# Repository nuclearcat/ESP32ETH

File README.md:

# ESP32ETH
Simple ESP32 with native ethernet using LAN8720 phy, Arduino compatible

Minimalistic design that can be extended. Manufactured and tested in real life, reliable, no packetloss, etc.

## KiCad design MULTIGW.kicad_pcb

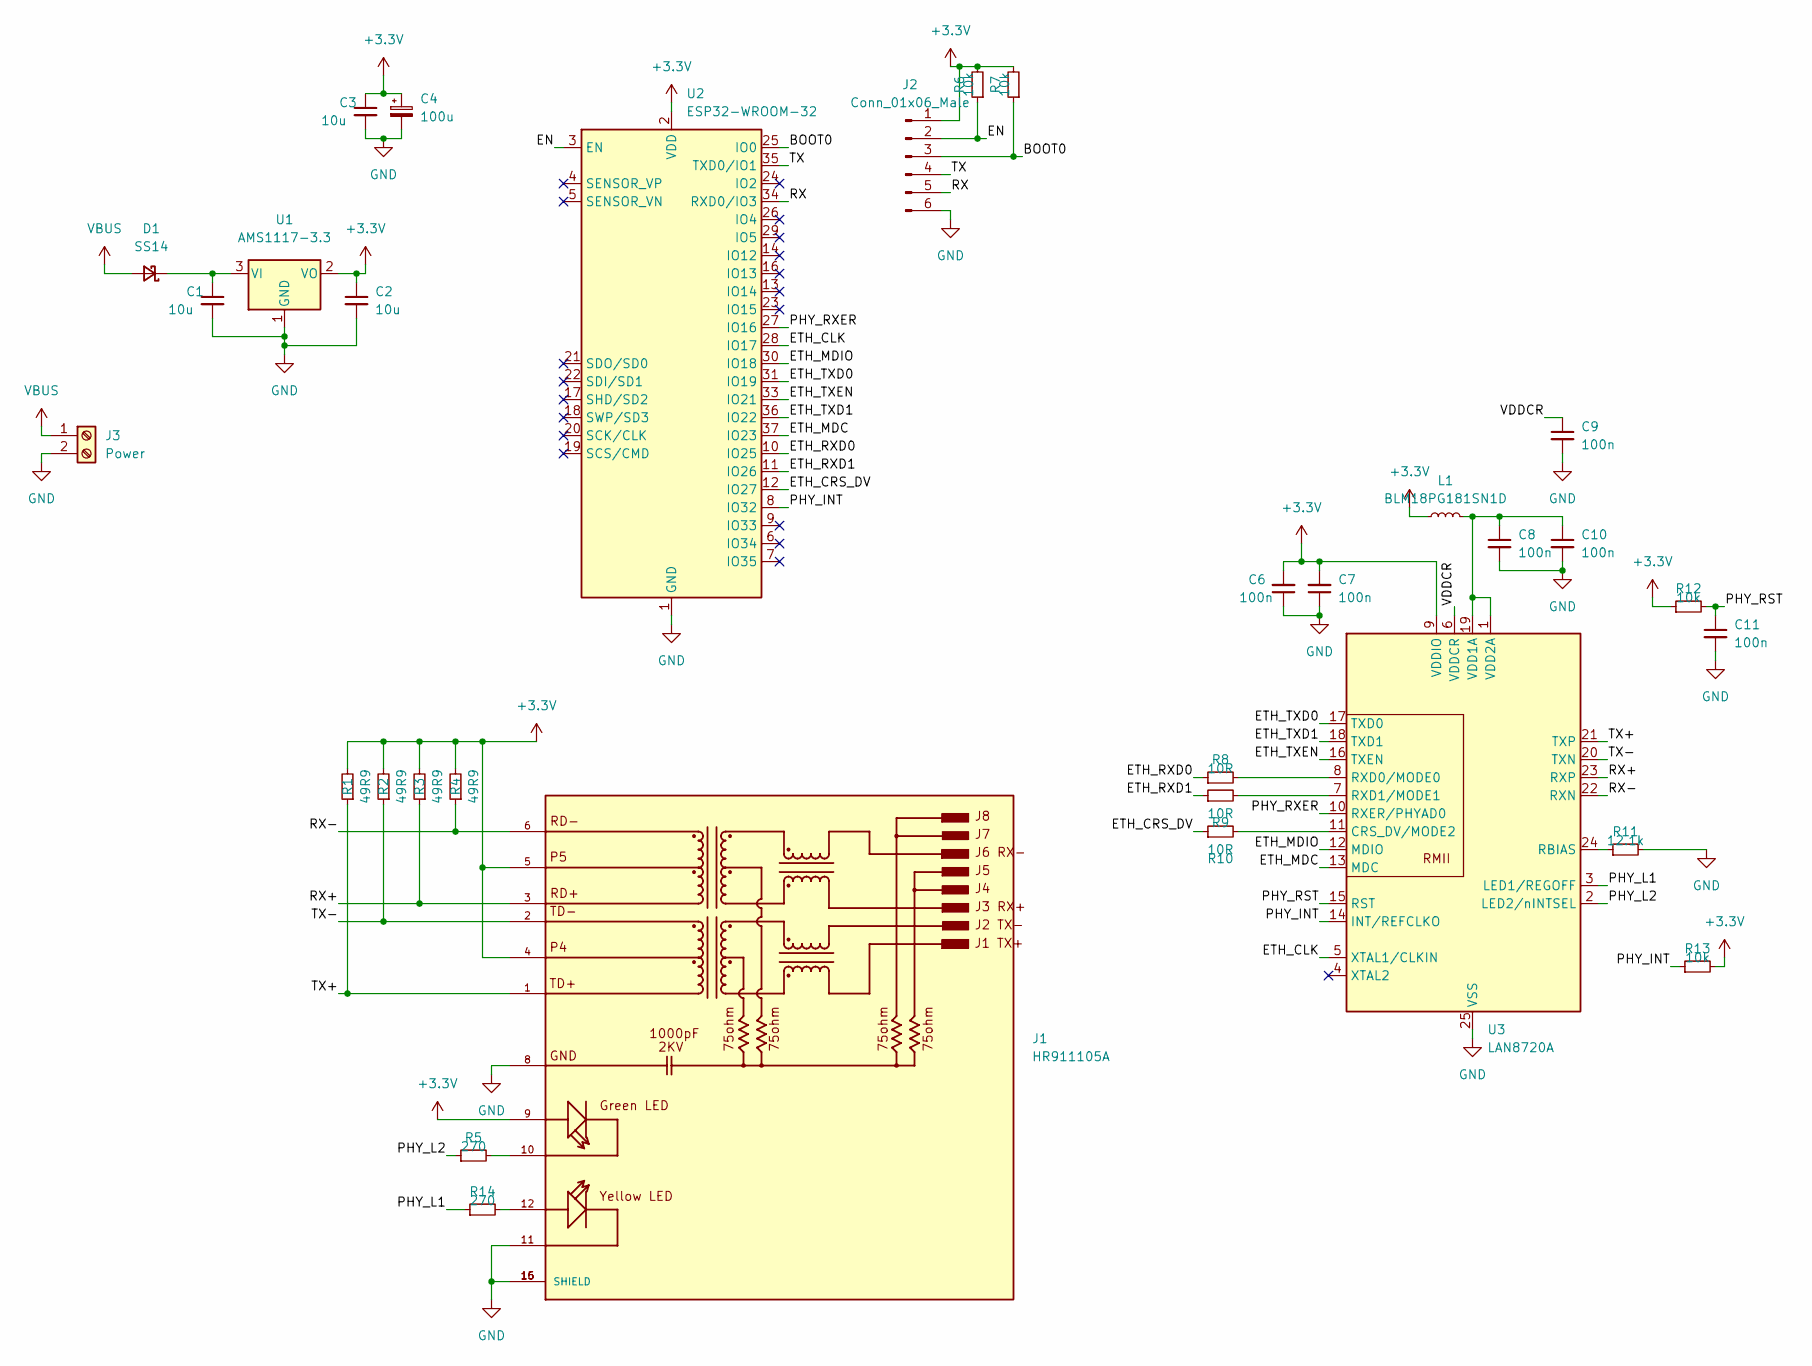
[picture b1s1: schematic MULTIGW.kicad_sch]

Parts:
C1: 10u; R_0603_1608Metric
C2, C3: 10u; C_0603_1608Metric
C4: 100u; CP_EIA-3528-21_Kemet-B
C6, C7, C8, C9, C10, C11: 100n; C_0603_1608Metric
D1: SS14; D_SMA
J1: HR911105A; HANRUN_HR911105A; PARTREV A
J2: Conn_01x06_Male; PinHeader_1x06_P2.54mm_Vertical
J3: Power; TerminalBlock_4Ucon_1x02_P3.50mm_Vertical
L1: BLM18PG181SN1D; R_0603_1608Metric
R1, R2, R3, R4: 49R9; R_0603_1608Metric
R5, R14: 270; R_0603_1608Metric
R6, R7, R12, R13: 10k; R_0603_1608Metric
R8, R9, R10: 10R; R_0603_1608Metric
R11: 12.1k; R_0603_1608Metric
U1: AMS1117-3.3; SOT-223-3_TabPin2
U2: ESP32-WROOM-32
U3: LAN8720A; QFN-24-1EP_4x4mm_P0.5mm_EP2.6x2.6mm

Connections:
+3V3: C2.1, C3.1, C4.1, C6.2, C7.2, J1.4, J1.5, J1.9, J2.1, L1.1, R1.2, R2.2, R3.2, R4.2, R6.2, R7.2, R12.1, R13.2, U1.2 (VO), U2.2 (VDD), U3.9 (VDDIO)
/BOOT0: J2.3, R7.1, U2.25 (IO0)
/EN: J2.2, R6.1, U2.3 (EN)
/ETH_CLK: U2.28 (IO17), U3.5 (XTAL1/CLKIN)
/ETH_CRS_DV: R10.1, U2.12 (IO27)
/ETH_MDC: U2.37 (IO23), U3.13 (MDC)
/ETH_MDIO: U2.30 (IO18), U3.12 (MDIO)
/ETH_RXD0: R8.1, U2.10 (IO25)
/ETH_RXD1: R9.1, U2.11 (IO26)
/ETH_TXD0: U2.31 (IO19), U3.17 (TXD0)
/ETH_TXD1: U2.36 (IO22), U3.18 (TXD1)
/ETH_TXEN: U2.33 (IO21), U3.16 (TXEN)
/PHY_INT: R13.1, U2.8 (IO32), U3.14 (INT/REFCLKO)
/PHY_L1: R14.1, U3.3 (LED1/REGOFF)
/PHY_L2: R5.1, U3.2 (LED2/nINTSEL)
/PHY_RST: C11.1, R12.2, U3.15 (RST)
/PHY_RXER: U2.27 (IO16), U3.10 (RXER/PHYAD0)
/RX: J2.5, U2.34 (RXD0/IO3)
/RX+: J1.3, R3.1, U3.23 (RXP)
/RX-: J1.6, R4.1, U3.22 (RXN)
/TX: J2.4, U2.35 (TXD0/IO1)
/TX+: J1.1, R1.1, U3.21 (TXP)
/TX-: J1.2, R2.1, U3.20 (TXN)
/VDDCR: C9.1, U3.6 (VDDCR)
GND: C1.2, C2.2, C3.2, C4.2, C6.1, C7.1, C8.2, C9.2, C10.2, C11.2, J1.8, J1.11, J1.15 (SHIELD), J1.16 (SHIELD), J2.6, J3.2, R11.2, U1.1 (GND), U2.1 (GND), U2.15 (GND), U2.38 (GND), U2.39 (GND), U3.25 (VSS)
unnamed: C1.1, D1.1 (K), U1.3 (VI)
unnamed: C8.1, C10.1, L1.2, U3.1 (VDD2A), U3.19 (VDD1A)
unnamed: J1.10, R5.2
unnamed: J1.12, R14.2
unnamed: R8.2, U3.8 (RXD0/MODE0)
unnamed: R9.2, U3.7 (RXD1/MODE1)
unnamed: R10.2, U3.11 (CRS_DV/MODE2)
unnamed: R11.1, U3.24 (RBIAS)
VBUS: D1.2 (A), J3.1

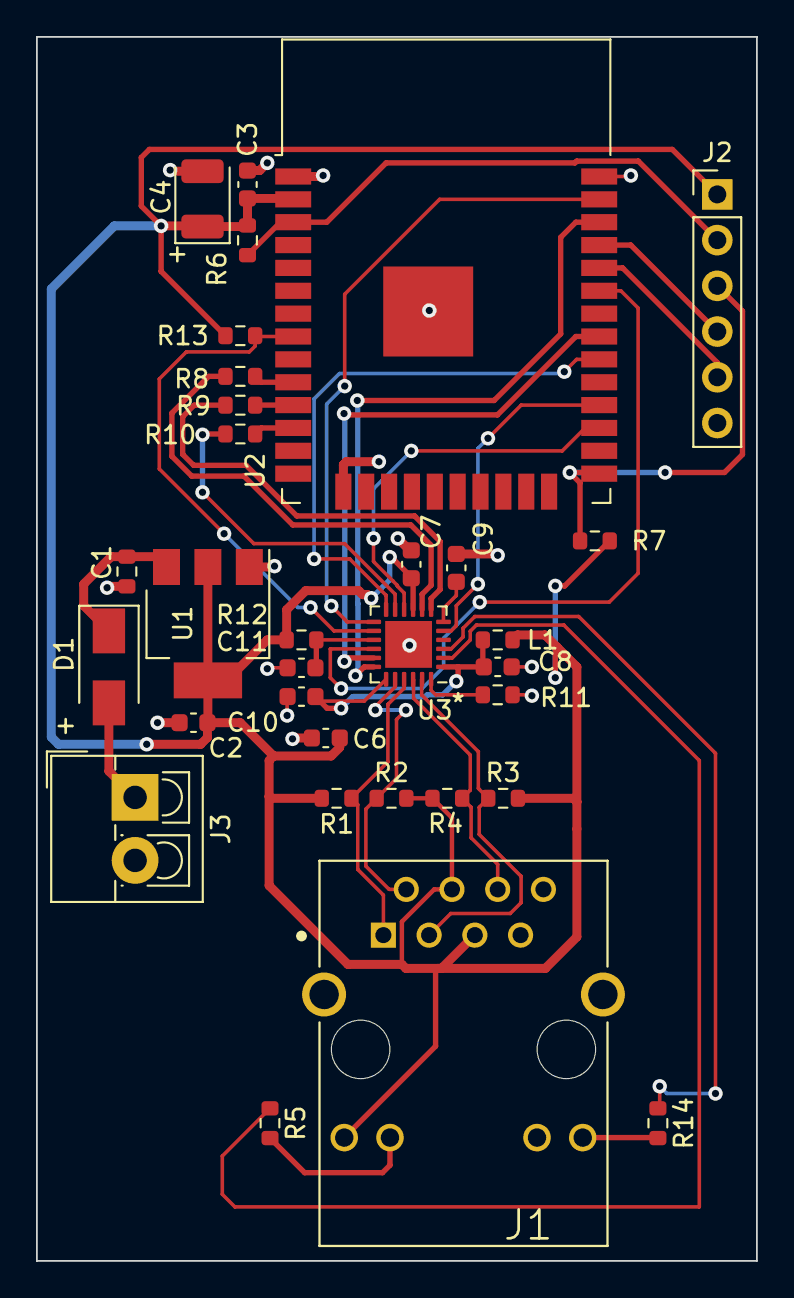
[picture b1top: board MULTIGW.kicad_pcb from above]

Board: 2 copper layers, 40.0 x 68.0 mm, 32 parts (0 on the bottom side), 34 nets.

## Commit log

2022-07-08 Verified design
2022-07-08 Small tidy up
2022-07-08 Add JLCPCB gerbers and PCBA files
